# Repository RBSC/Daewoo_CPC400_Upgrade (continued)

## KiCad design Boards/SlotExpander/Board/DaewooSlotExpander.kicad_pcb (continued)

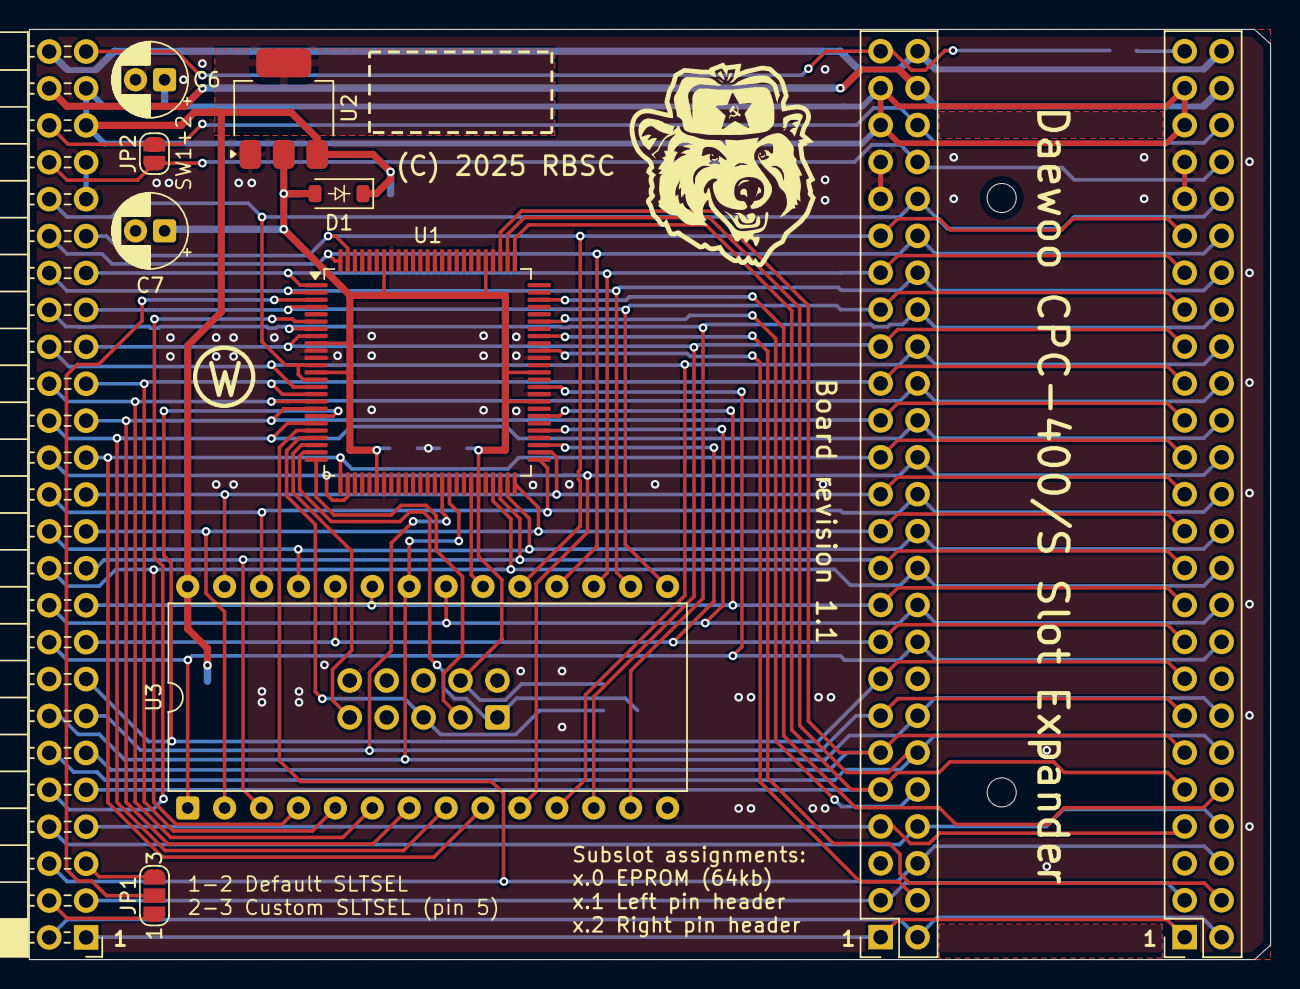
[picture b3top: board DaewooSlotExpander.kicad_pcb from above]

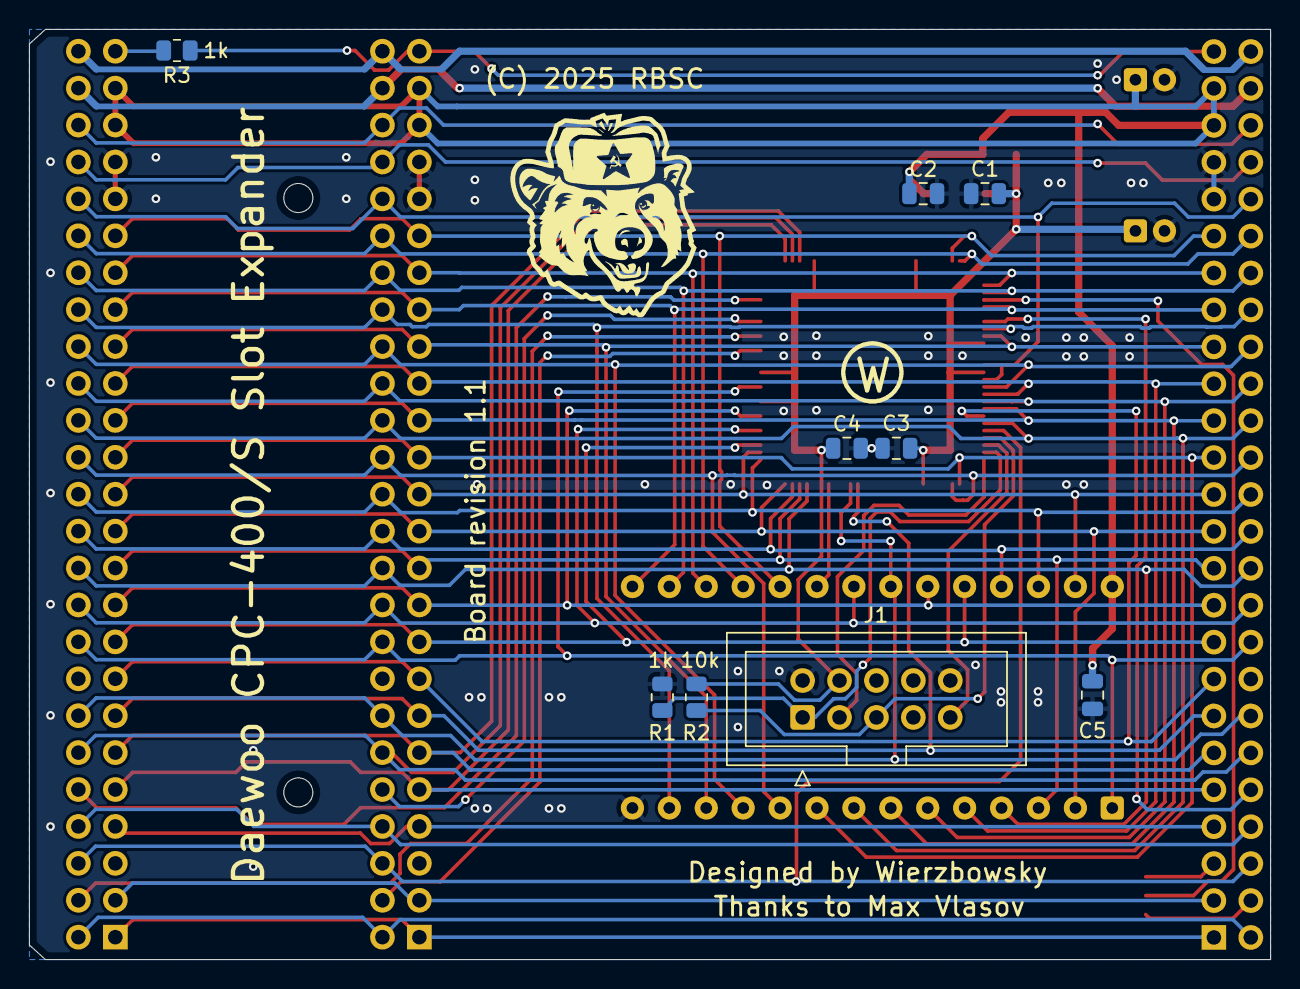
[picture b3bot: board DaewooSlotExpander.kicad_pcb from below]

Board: 2 copper layers, 85.4 x 64.0 mm, 20 parts (9 on the bottom side), 59 nets.

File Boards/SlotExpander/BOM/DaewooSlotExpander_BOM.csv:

"Id";"Designator";"Footprint";"Quantity";"Designation";"Supplier and ref";
1;"D1";"D_SOD-123";1;"1N4148W";;;
2;"C6,C7";"CP_Radial_D5.0mm_P2.00mm";2;"100uF 16V";;;
3;"U2";"SOT-223-3_TabPin2";1;"AMS1117-3.3";;;
4;"U3";"DIP-28_W15.24mm";1;"27C512";;;
5;"BUS_Expansion2,BUS_Expansion3";"PinHeader_2x25_P2.54mm_Vertical";2;"my_components_MSX_SLOT_HOST";;;
6;"BUS_Expansion1";"DaewooBackSlotConnector";1;"my_components_MSX_SLOT_HOST";;;
7;"U1";"LQFP-100_14x14mm_P0.5mm";1;"EPM240T100";;;
8;"C2,C5,C1,C3,C4";"C_0805_2012Metric";5;"100nF";;;
9;"J1";"IDC-Header_2x05_P2.54mm_Vertical";1;"AVR-JTAG-10";;;
10;"R2";"R_0805_2012Metric";1;"10k";;;
11;"R1,R3";"R_0805_2012Metric";2;"1k";;;

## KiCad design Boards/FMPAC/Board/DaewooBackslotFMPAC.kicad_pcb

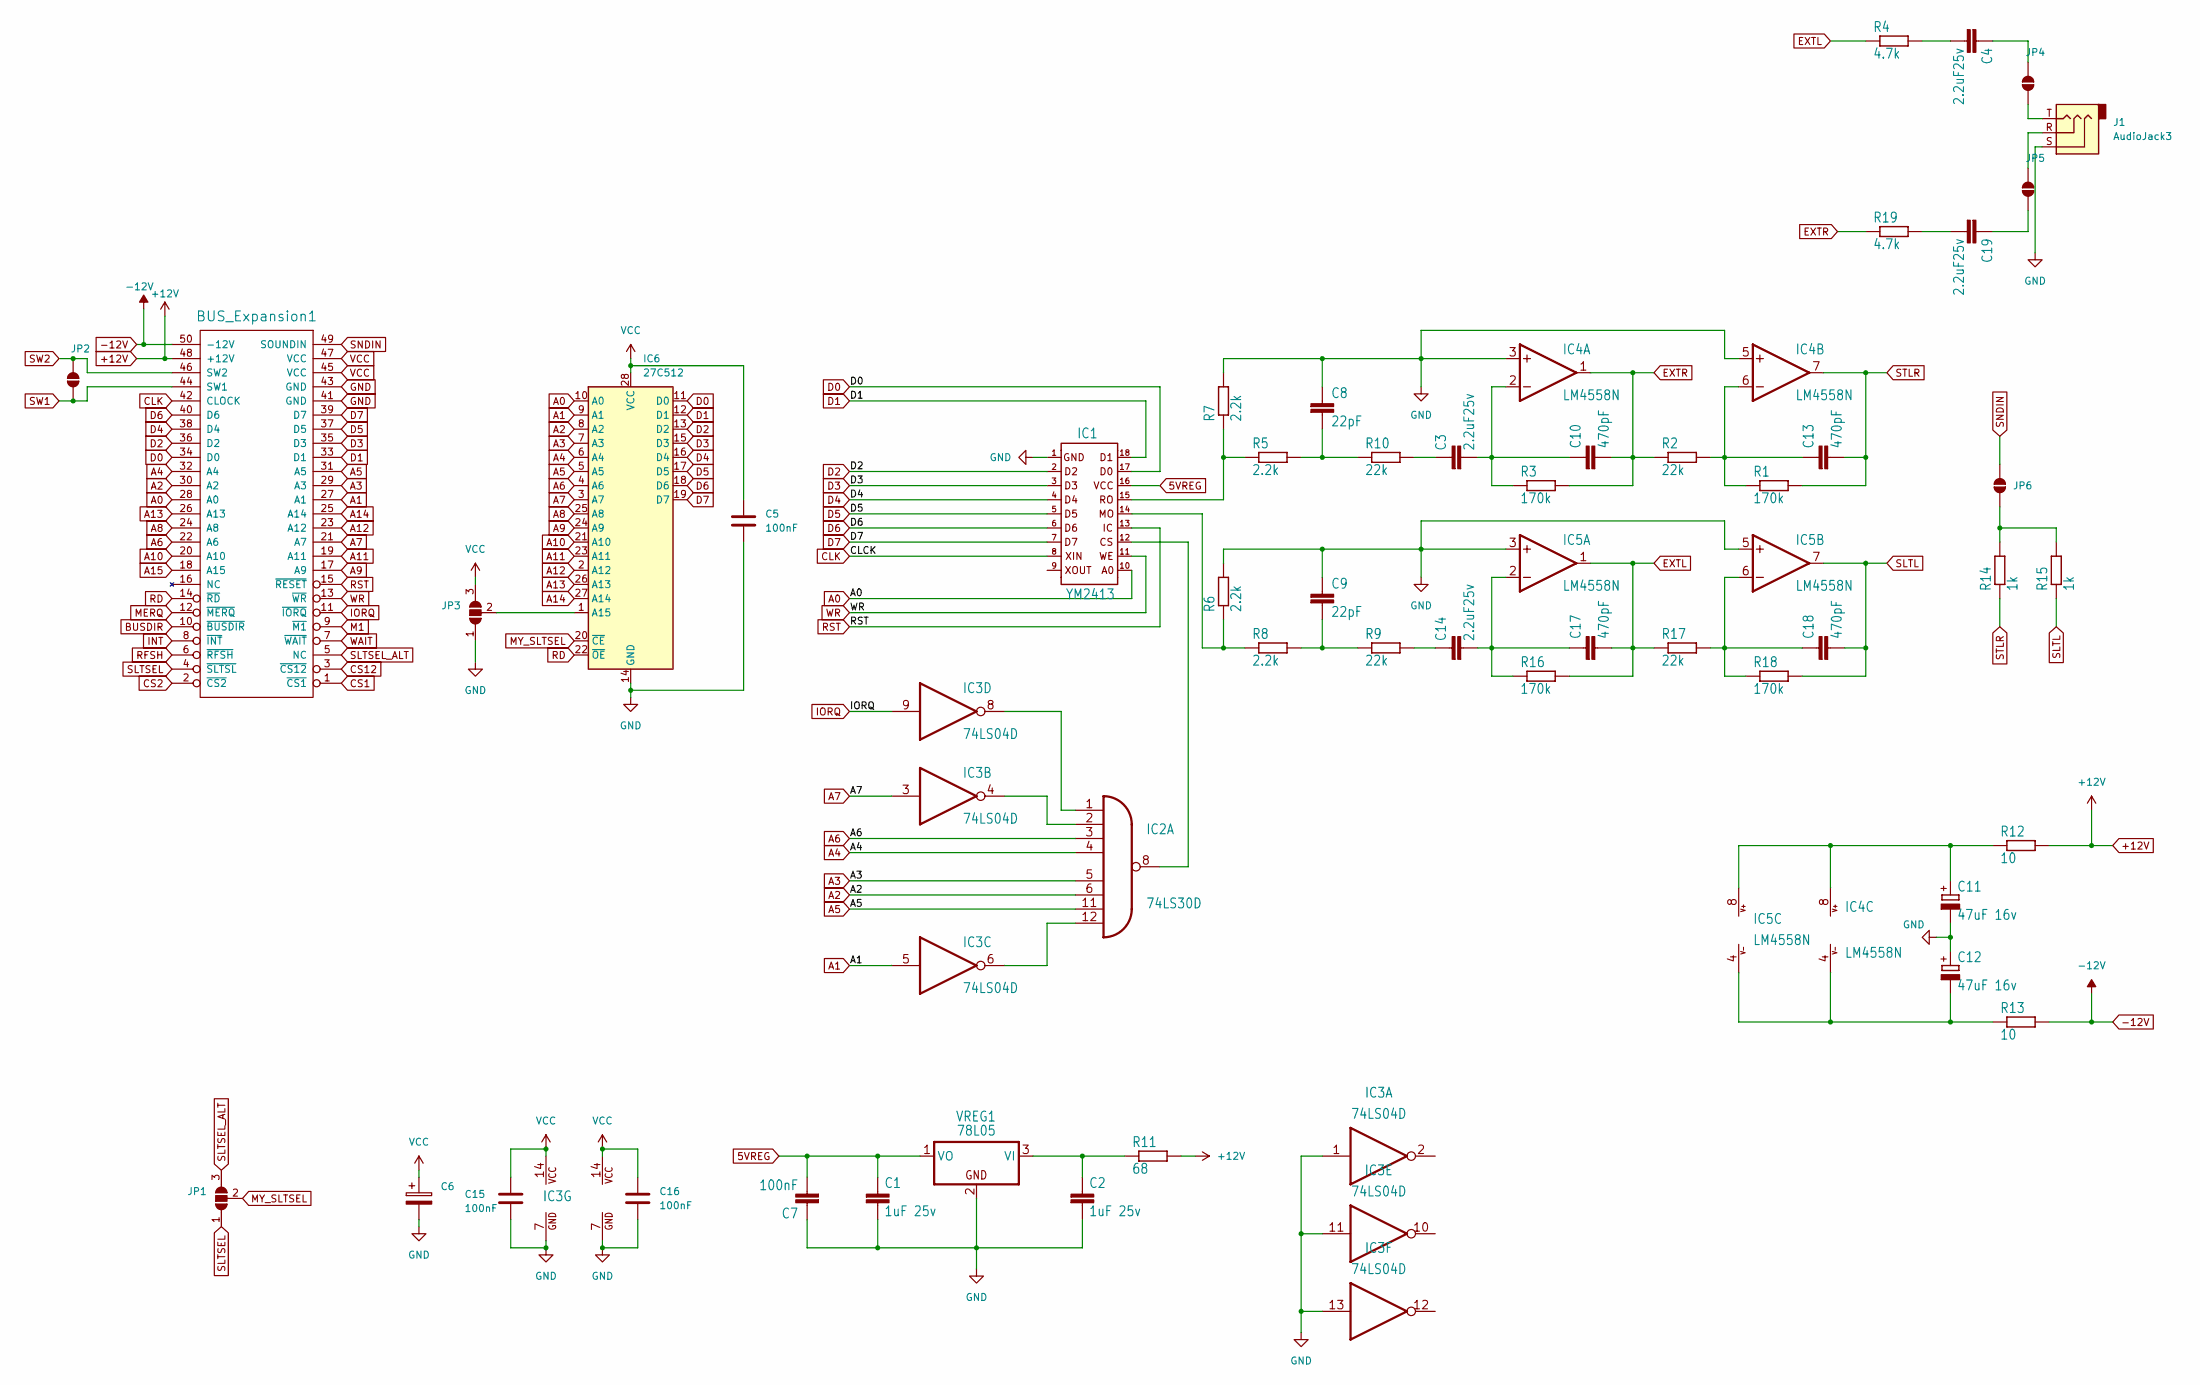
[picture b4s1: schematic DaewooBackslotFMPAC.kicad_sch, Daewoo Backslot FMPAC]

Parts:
BUS_Expansion1: my_components_MSX_SLOT_HOST; DaewooBackSlotConnector
C1, C2: 1uF 25v; C_1210_3225Metric
C3, C4, C14, C19: 2.2uF25v; C_1210_3225Metric
C5, C7, C15, C16: 100nF; C_0805_2012Metric
C6: 100uF 16V; CP_Radial_D5.0mm_P2.00mm
C8, C9: 22pF; C_0805_2012Metric
C10, C13, C17, C18: 470pF; C_0805_2012Metric
C11, C12: 47uF 16v; CP_Radial_D5.0mm_P2.00mm
IC1: YM2413; DIP-18_W7.62mm_LongPads
IC2: 74LS30D; SO-14_3.9x8.65mm_P1.27mm
IC3: 74LS04D; SO-14_3.9x8.65mm_P1.27mm
IC4, IC5: LM4558N; SOIC-8_3.9x4.9mm_P1.27mm
IC6: 27C512; DIP-28_W15.24mm
J1: AudioJack3; Jack_3.5mm_CUI_SJ1-3525N_Horizontal
JP1, JP3: SolderJumper_3_Open; SolderJumper-3_P1.3mm_Open_RoundedPad1.0x1.5mm_NumberLabels
JP2, JP4, JP5, JP6: SolderJumper_2_Open; SolderJumper-2_P1.3mm_Open_RoundedPad1.0x1.5mm
R1, R3, R16, R18: 170k; R_0805_2012Metric
R2, R9, R10, R17: 22k; R_0805_2012Metric
R4, R19: 4.7k; R_0805_2012Metric
R5, R6, R7, R8: 2.2k; R_0805_2012Metric
R11: 68; R_0805_2012Metric
R12, R13: 10; R_0805_2012Metric
R14, R15: 1k; R_0805_2012Metric
VREG1: 78L05; TO-92

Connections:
5VREG: C1.1, C7.2, IC1.16, VREG1.1 (VO)
+12V: BUS_Expansion1.48 (+12V), C11.1, R11.2, R12.2
-12V: BUS_Expansion1.50 (-12V), C12.2, R13.2
A0: BUS_Expansion1.28 (A0), IC1.10, IC6.10 (A0)
A1: BUS_Expansion1.27 (A1), IC3.5 (I), IC6.9 (A1)
A2: BUS_Expansion1.30 (A2), IC2.6 (I5), IC6.8 (A2)
A3: BUS_Expansion1.29 (A3), IC2.5 (I4), IC6.7 (A3)
A4: BUS_Expansion1.32 (A4), IC2.4 (I3), IC6.6 (A4)
A5: BUS_Expansion1.31 (A5), IC2.11 (I6), IC6.5 (A5)
A6: BUS_Expansion1.22 (A6), IC2.3 (I2), IC6.4 (A6)
A7: BUS_Expansion1.21 (A7), IC3.3 (I), IC6.3 (A7)
A8: BUS_Expansion1.24 (A8), IC6.25 (A8)
A9: BUS_Expansion1.17 (A9), IC6.24 (A9)
A10: BUS_Expansion1.20 (A10), IC6.21 (A10)
A11: BUS_Expansion1.19 (A11), IC6.23 (A11)
A12: BUS_Expansion1.23 (A12), IC6.2 (A12)
A13: BUS_Expansion1.26 (A13), IC6.26 (A13)
A14: BUS_Expansion1.25 (A14), IC6.27 (A14)
A15: BUS_Expansion1.18 (A15)
BUSDIR: BUS_Expansion1.10 (~BUSDIR)
CLK: BUS_Expansion1.42 (CLOCK), IC1.8
CS1: BUS_Expansion1.1 (~CS1)
CS2: BUS_Expansion1.2 (~CS2)
CS12: BUS_Expansion1.3 (~CS12)
D0: BUS_Expansion1.34 (D0), IC1.17, IC6.11 (D0)
D1: BUS_Expansion1.33 (D1), IC1.18, IC6.12 (D1)
D2: BUS_Expansion1.36 (D2~), IC1.2, IC6.13 (D2)
D3: BUS_Expansion1.35 (D3), IC1.3, IC6.15 (D3)
D4: BUS_Expansion1.38 (D4), IC1.4, IC6.16 (D4)
D5: BUS_Expansion1.37 (D5), IC1.5, IC6.17 (D5)
D6: BUS_Expansion1.40 (D6), IC1.6, IC6.18 (D6)
D7: BUS_Expansion1.39 (D7), IC1.7, IC6.19 (D7)
EXTL: C17.2, IC5.1 (OUT), R4.1, R16.2, R17.1
EXTR: C10.2, IC4.1 (OUT), R2.1, R3.2, R19.1
GND: BUS_Expansion1.41 (GND), BUS_Expansion1.43 (GND), C1.2, C2.2, C5.2, C6.2, C7.1, C8.1, C9.1, C11.-, C12.+, C15.2, C16.2, IC1.1, IC2.7 (GND), IC3.1 (I), IC3.7 (GND), IC3.11 (I), IC3.13 (I), IC4.3 (+IN), IC4.5 (+IN), IC5.3 (+IN), IC5.5 (+IN), IC6.14 (GND), J1.S, JP3.1 (A), R6.2, R7.2, VREG1.2 (GND)
INT: BUS_Expansion1.8 (~INT)
IORQ: BUS_Expansion1.11 (~IORQ), IC3.9 (I)
M1: BUS_Expansion1.9 (~M1)
MERQ: BUS_Expansion1.12 (~MERQ)
MY_SLTSEL: IC6.20 (~CE), JP1.2 (C)
unnamed: C3.1, R10.2
unnamed: C4.2, R4.2
unnamed: C8.2, R5.2, R10.1
unnamed: C9.2, R8.2, R9.1
unnamed: C14.1, R9.2
unnamed: C19.2, R19.2
unnamed: IC1.14, R6.1, R8.1
unnamed: IC1.15, R5.1, R7.1
unnamed: IC2.1 (I0), IC3.8 (O)
unnamed: IC2.2 (I1), IC3.4 (O)
unnamed: IC2.12 (I7), IC3.6 (O)
unnamed: IC1.12, IC2.8 (O)
unnamed: C3.2, C10.1, IC4.2 (-IN), R3.1
unnamed: C13.1, IC4.6 (-IN), R1.1, R2.2
unnamed: C11.+, IC4.8 (V+), IC5.8 (V+), R12.1
unnamed: C12.-, IC4.4 (V-), IC5.4 (V-), R13.1
unnamed: C14.2, C17.1, IC5.2 (-IN), R16.1
unnamed: C18.1, IC5.6 (-IN), R17.2, R18.1
unnamed: IC6.1 (A15), JP3.2 (C)
unnamed: J1.T, JP4.1 (A)
unnamed: C4.1, JP4.2 (B)
unnamed: C19.1, JP5.1 (A)
unnamed: J1.R, JP5.2 (B)
unnamed: JP6.1 (A), R14.2, R15.2
unnamed: C2.1, R11.1, VREG1.3 (VI)
RD: BUS_Expansion1.14 (~RD), IC6.22 (~OE)
RFSH: BUS_Expansion1.6 (~RFSH)
RST: BUS_Expansion1.15 (~RESET), IC1.13
SLTL: C18.2, IC5.7 (OUT), R15.1, R18.2
SLTSEL: BUS_Expansion1.4 (~SLTSL), JP1.1 (A)
SLTSEL_ALT: BUS_Expansion1.5 (NC), JP1.3 (B)
SNDIN: BUS_Expansion1.49 (SOUNDIN), JP6.2 (B)
STLR: C13.2, IC4.7 (OUT), R1.2, R14.1
SW1: BUS_Expansion1.44 (SW1), JP2.1 (A)
SW2: BUS_Expansion1.46 (SW2), JP2.2 (B)
VCC: BUS_Expansion1.45 (VCC), BUS_Expansion1.47 (VCC), C5.1, C6.1, C15.1, C16.1, IC2.14 (VCC), IC3.14 (VCC), IC6.28 (VCC), JP3.3 (B)
WAIT: BUS_Expansion1.7 (~WAIT)
WR: BUS_Expansion1.13 (~WR), IC1.11

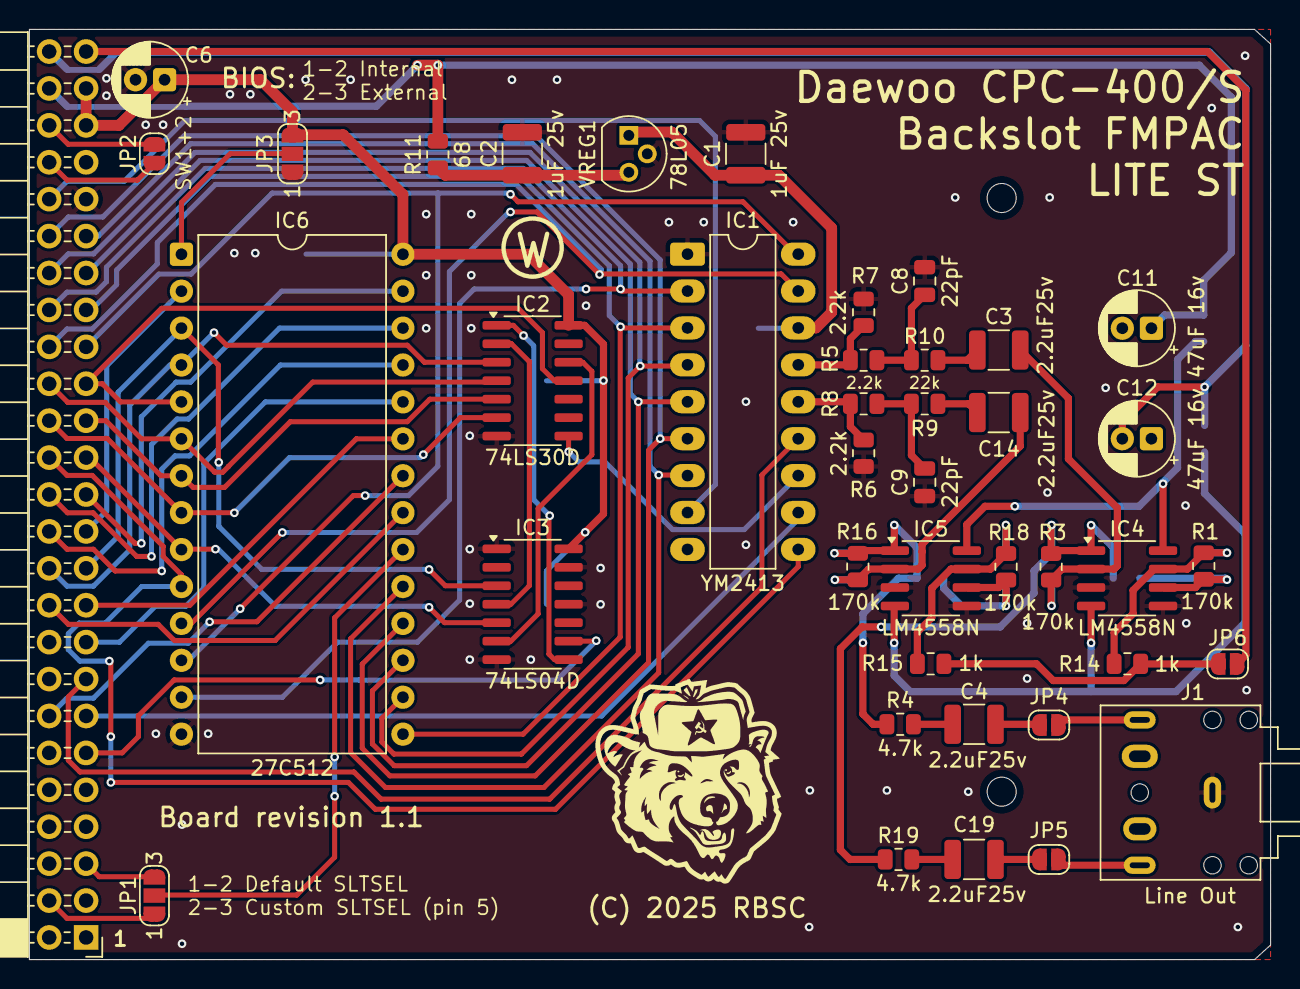
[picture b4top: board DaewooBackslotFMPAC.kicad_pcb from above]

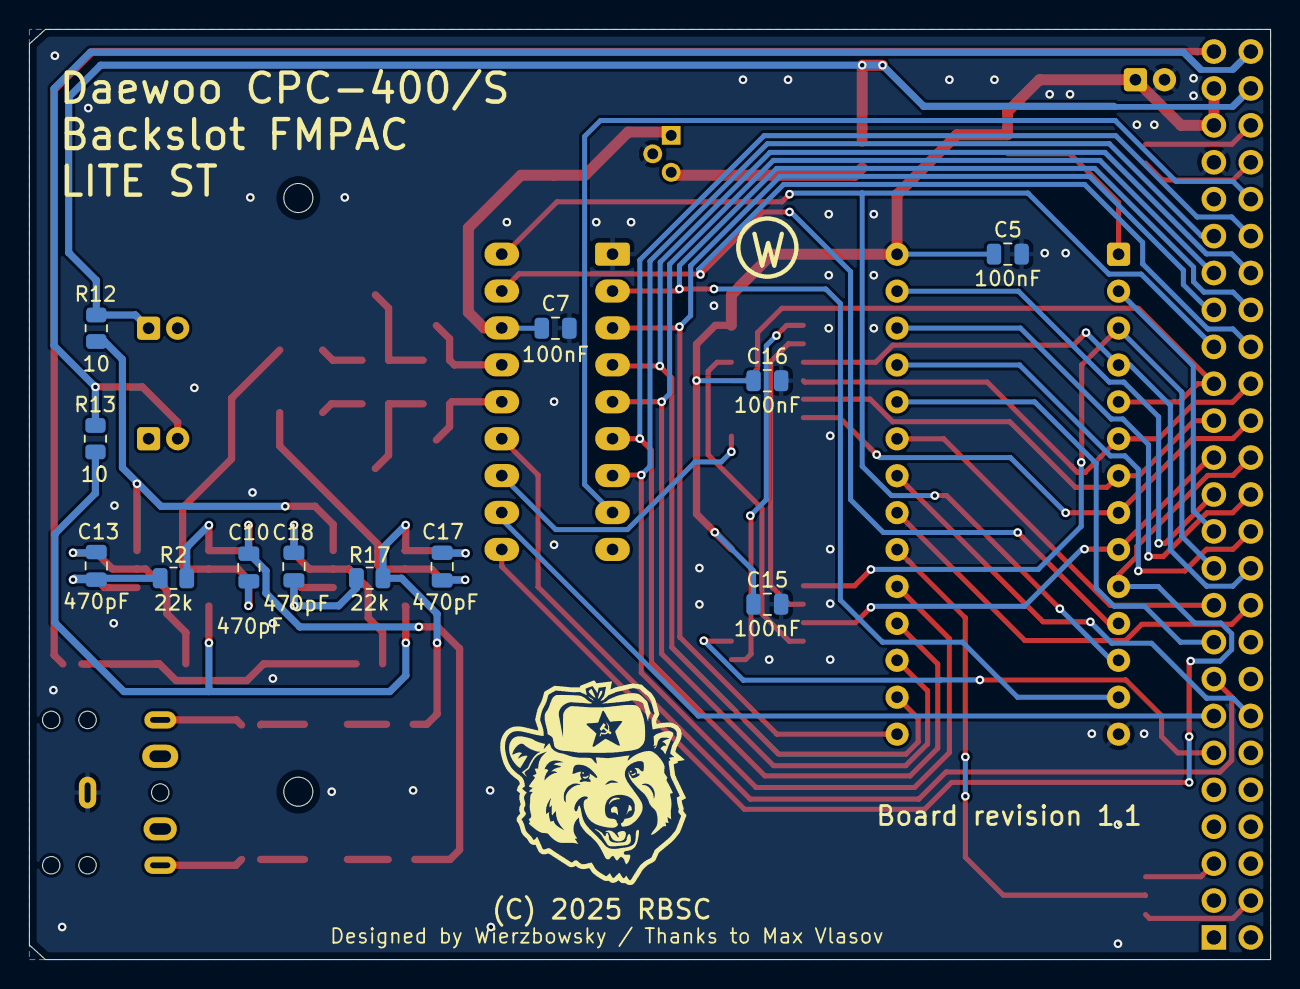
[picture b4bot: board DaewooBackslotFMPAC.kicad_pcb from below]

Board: 2 copper layers, 85.4 x 64.0 mm, 53 parts (12 on the bottom side), 68 nets.

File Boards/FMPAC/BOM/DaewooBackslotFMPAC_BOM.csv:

"Id";"Designator";"Footprint";"Quantity";"Designation";"Supplier and ref";
1;"J1";"Jack_3.5mm_CUI_SJ1-3525N_Horizontal";1;"Line Out";;;
2;"VREG1";"TO-92";1;"78L05";;;
3;"C9,C8";"C_0805_2012Metric";2;"22pF";;;
4;"R8,R5,R6,R7";"R_0805_2012Metric";4;"2.2k";;;
5;"IC1";"DIP-18_W7.62mm_LongPads";1;"YM2413";;;
6;"IC4,IC5";"SOIC-8_3.9x4.9mm_P1.27mm";2;"LM4558N";;;
7;"C12,C11";"CP_Radial_D5.0mm_P2.00mm";2;"47uF 16v";;;
8;"C1,C2";"C_1210_3225Metric";2;"1uF 25v";;;
9;"R19,R4";"R_0805_2012Metric";2;"4.7k";;;
10;"R16,R3,R1,R18";"R_0805_2012Metric";4;"170k";;;
11;"R11";"R_0805_2012Metric";1;"68";;;
12;"C3,C14,C19,C4";"C_1210_3225Metric";4;"2.2uF25v";;;
13;"IC2";"SO-14_3.9x8.65mm_P1.27mm";1;"74LS30D";;;
14;"R9,R10,R17,R2";"R_0805_2012Metric";4;"22k";;;
15;"C6";"CP_Radial_D5.0mm_P2.00mm";1;"100uF 16V";;;
16;"IC6";"DIP-28_W15.24mm";1;"27C512";;;
17;"IC3";"SO-14_3.9x8.65mm_P1.27mm";1;"74LS04D";;;
18;"BUS_Expansion1";"DaewooBackSlotConnector";1;"my_components_MSX_SLOT_HOST";;;
19;"C10,C13,C17,C18";"C_0805_2012Metric";4;"470pF";;;
20;"R12,R13";"R_0805_2012Metric";2;"10";;;
21;"C15,C5,C7,C16";"C_0805_2012Metric";4;"100nF";;;
22;"R14,R15";"R_0805_2012Metric";2;"1k";;;

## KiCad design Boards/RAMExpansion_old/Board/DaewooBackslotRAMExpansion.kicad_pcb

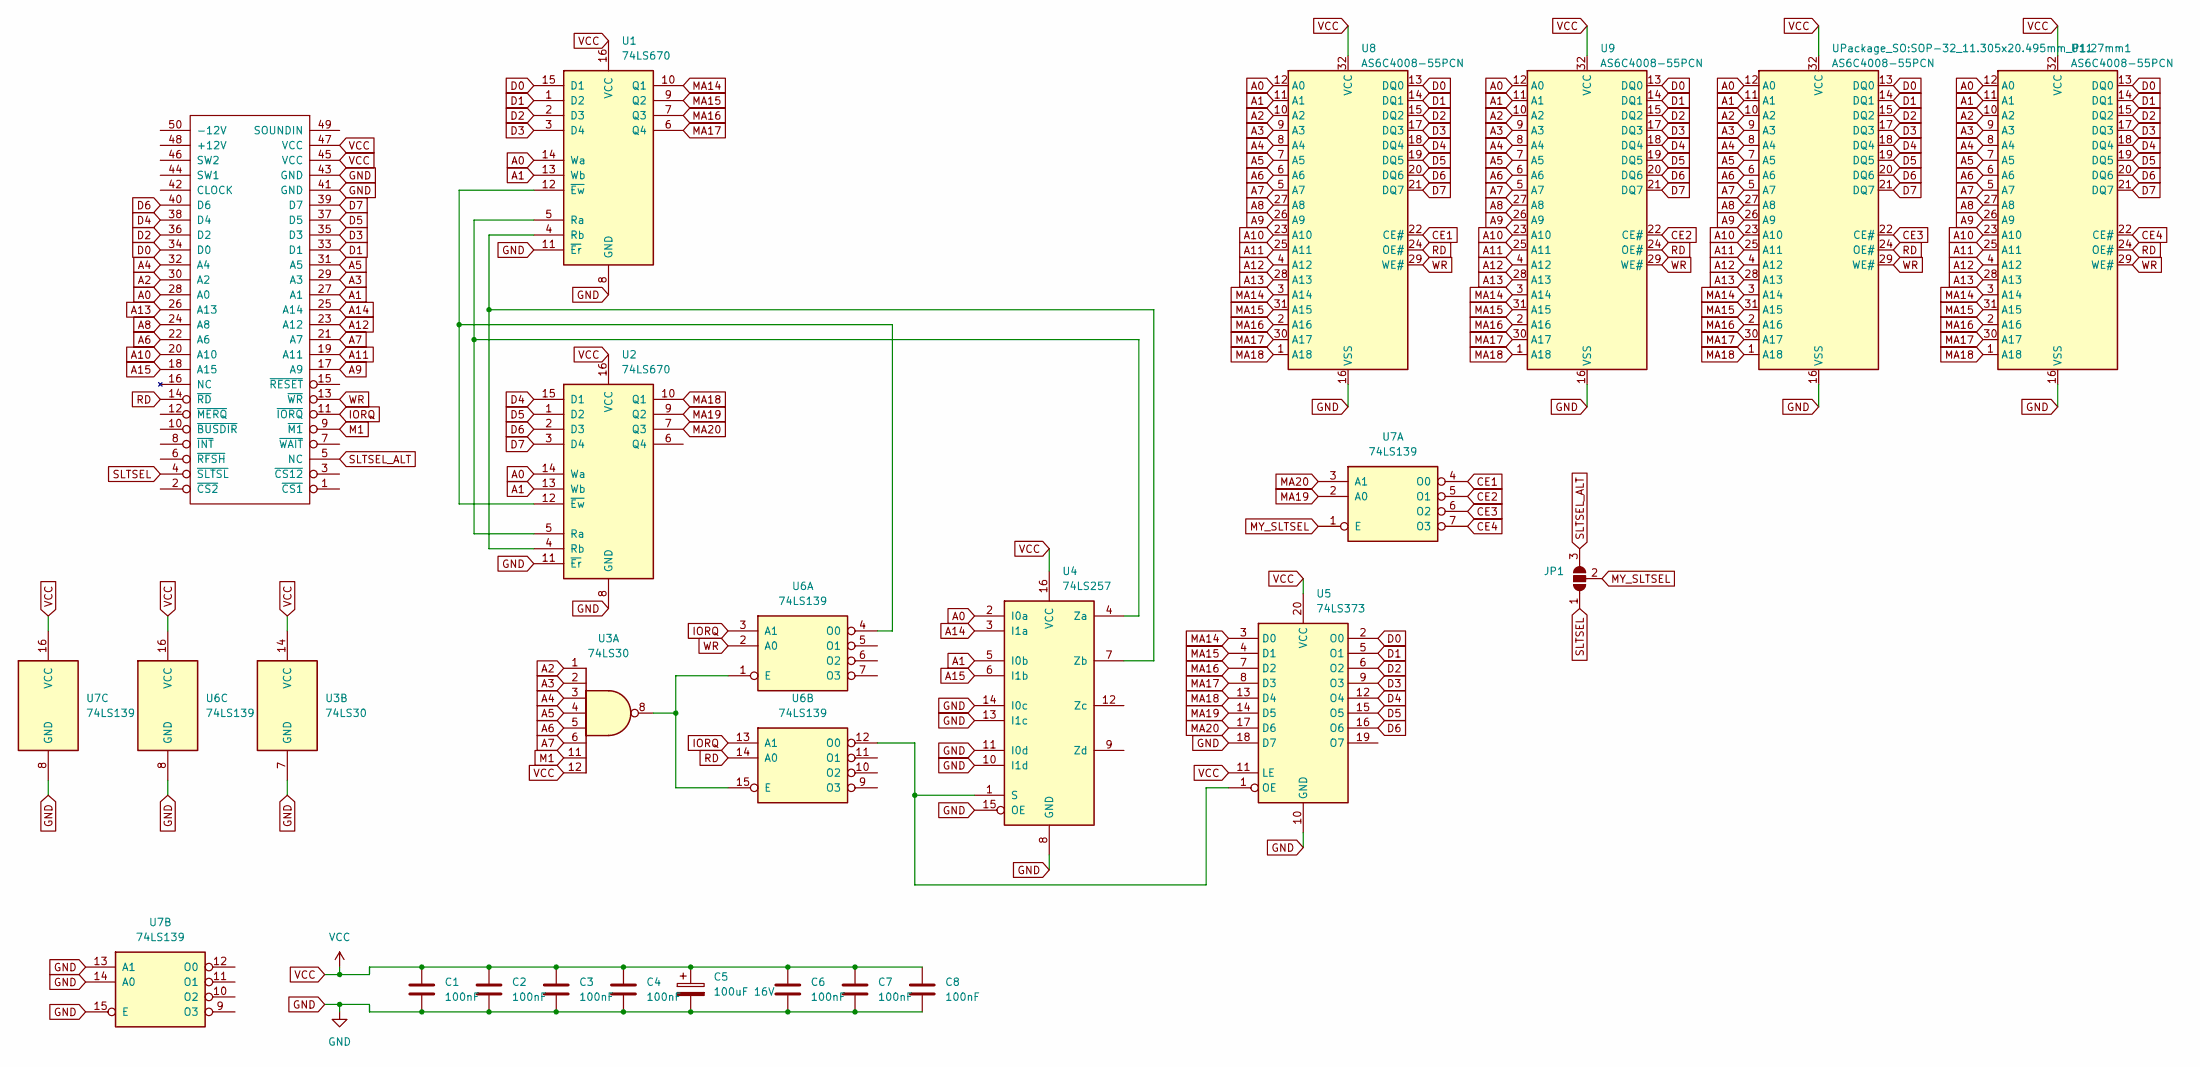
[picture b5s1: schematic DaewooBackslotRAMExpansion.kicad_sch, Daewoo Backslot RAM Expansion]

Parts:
BUS1: my_components_MSX_SLOT_HOST; DaewooBackSlotConnector
C1, C2, C3, C4, C6, C7, C8: 100nF; C_0805_2012Metric
C5: 100uF 16V; CP_Radial_D5.0mm_P2.00mm
JP1: SolderJumper_3_Open; SolderJumper-3_P1.3mm_Open_RoundedPad1.0x1.5mm_NumberLabels
U1, U2: 74LS670; SO-16_3.9x9.9mm_P1.27mm
U3: 74LS30; SO-14_3.9x8.65mm_P1.27mm
U4: 74LS257; SO-16_3.9x9.9mm_P1.27mm
U5: 74LS373; SOIC-20W_7.5x12.8mm_P1.27mm
U6, U7: 74LS139; SO-16_3.9x9.9mm_P1.27mm
U8, U9, U11: AS6C4008-55PCN; SOP-32_11.305x20.495mm_P1.27mm
UPackage_SO:SOP-32_11.305x20.495mm_P1.27mm1: AS6C4008-55PCN; SOP-32_11.305x20.495mm_P1.27mm

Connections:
A0: BUS1.28 (A0), U1.14 (Wa), U2.14 (Wa), U4.2 (I0a), U8.12 (A0), U9.12 (A0), U11.12 (A0), UPackage_SO:SOP-32_11.305x20.495mm_P1.2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.12 (A0); also elsewhere on the board
A1: BUS1.27 (A1), U1.13 (Wb), U2.13 (Wb), U4.5 (I0b), U8.11 (A1), U9.11 (A1), U11.11 (A1), UPackage_SO:SOP-32_11.305x20.495mm_P1.2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.11 (A1); also elsewhere on the board
A2: BUS1.30 (A2), U3.1, U8.10 (A2), U9.10 (A2), U11.10 (A2), UPackage_SO:SOP-32_11.305x20.495mm_P1.2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.10 (A2); also elsewhere on the board
A3: BUS1.29 (A3), U3.2, U8.9 (A3), U9.9 (A3), U11.9 (A3), UPackage_SO:SOP-32_11.305x20.495mm_P1.2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.9 (A3); also elsewhere on the board
A4: BUS1.32 (A4), U3.3, U8.8 (A4), U9.8 (A4), U11.8 (A4), UPackage_SO:SOP-32_11.305x20.495mm_P1.2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.8 (A4); also elsewhere on the board
A5: BUS1.31 (A5), U3.4, U8.7 (A5), U9.7 (A5), U11.7 (A5), UPackage_SO:SOP-32_11.305x20.495mm_P1.2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.7 (A5); also elsewhere on the board
A6: BUS1.22 (A6), U3.5, U8.6 (A6), U9.6 (A6), U11.6 (A6), UPackage_SO:SOP-32_11.305x20.495mm_P1.2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.6 (A6); also elsewhere on the board
A7: BUS1.21 (A7), U3.6, U8.5 (A7), U9.5 (A7), U11.5 (A7), UPackage_SO:SOP-32_11.305x20.495mm_P1.2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.5 (A7); also elsewhere on the board
A8: BUS1.24 (A8), U8.27 (A8), U9.27 (A8), U11.27 (A8), UPackage_SO:SOP-32_11.305x20.495mm_P1.2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.27 (A8); also elsewhere on the board
A9: BUS1.17 (A9), U8.26 (A9), U9.26 (A9), U11.26 (A9), UPackage_SO:SOP-32_11.305x20.495mm_P1.2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.26 (A9); also elsewhere on the board
A10: BUS1.20 (A10), U8.23 (A10), U9.23 (A10), U11.23 (A10), UPackage_SO:SOP-32_11.305x20.495mm_P1.2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.23 (A10); also elsewhere on the board
A11: BUS1.19 (A11), U8.25 (A11), U9.25 (A11), U11.25 (A11), UPackage_SO:SOP-32_11.305x20.495mm_P1.2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.25 (A11); also elsewhere on the board
A12: BUS1.23 (A12), U8.4 (A12), U9.4 (A12), U11.4 (A12), UPackage_SO:SOP-32_11.305x20.495mm_P1.2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.4 (A12); also elsewhere on the board
A13: BUS1.26 (A13), U8.28 (A13), U9.28 (A13), U11.28 (A13), UPackage_SO:SOP-32_11.305x20.495mm_P1.2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.28 (A13); also elsewhere on the board
A14: BUS1.25 (A14), U4.3 (I1a)
A15: BUS1.18 (A15), U4.6 (I1b)
CE1: U7.4 (O0), U8.22 (CE#)
CE2: U7.5 (O1), U9.22 (CE#)
CE3: U7.6 (O2), UPackage_SO:SOP-32_11.305x20.495mm_P1.2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.22 (CE#); also elsewhere on the board
CE4: U7.7 (O3), U11.22 (CE#)
D0: BUS1.34 (D0), U1.15 (D1), U5.2 (O0), U8.13 (DQ0), U9.13 (DQ0), U11.13 (DQ0), UPackage_SO:SOP-32_11.305x20.495mm_P1.2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.13 (DQ0); also elsewhere on the board
D1: BUS1.33 (D1), U1.1 (D2), U5.5 (O1), U8.14 (DQ1), U9.14 (DQ1), U11.14 (DQ1), UPackage_SO:SOP-32_11.305x20.495mm_P1.2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.14 (DQ1); also elsewhere on the board
D2: BUS1.36 (D2~), U1.2 (D3), U5.6 (O2), U8.15 (DQ2), U9.15 (DQ2), U11.15 (DQ2), UPackage_SO:SOP-32_11.305x20.495mm_P1.2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.15 (DQ2); also elsewhere on the board
D3: BUS1.35 (D3), U1.3 (D4), U5.9 (O3), U8.17 (DQ3), U9.17 (DQ3), U11.17 (DQ3), UPackage_SO:SOP-32_11.305x20.495mm_P1.2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.17 (DQ3); also elsewhere on the board
D4: BUS1.38 (D4), U2.15 (D1), U5.12 (O4), U8.18 (DQ4), U9.18 (DQ4), U11.18 (DQ4), UPackage_SO:SOP-32_11.305x20.495mm_P1.2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.18 (DQ4); also elsewhere on the board
D5: BUS1.37 (D5), U2.1 (D2), U5.15 (O5), U8.19 (DQ5), U9.19 (DQ5), U11.19 (DQ5), UPackage_SO:SOP-32_11.305x20.495mm_P1.2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.19 (DQ5); also elsewhere on the board
D6: BUS1.40 (D6), U2.2 (D3), U5.16 (O6), U8.20 (DQ6), U9.20 (DQ6), U11.20 (DQ6), UPackage_SO:SOP-32_11.305x20.495mm_P1.2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.20 (DQ6); also elsewhere on the board
D7: BUS1.39 (D7), U2.3 (D4), U8.21 (DQ7), U9.21 (DQ7), U11.21 (DQ7), UPackage_SO:SOP-32_11.305x20.495mm_P1.2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.21 (DQ7); also elsewhere on the board
GND: BUS1.41 (GND), BUS1.43 (GND), C1.2, C2.2, C3.2, C4.2, C5.2, C6.2, C7.2, C8.2, U1.8 (GND), U1.11 (~Er), U2.8 (GND), U2.11 (~Er), U3.7 (GND), U4.8 (GND), U4.10 (I1d), U4.11 (I0d), U4.13 (I1c), U4.14 (I0c), U4.15 (OE), U5.10 (GND), U5.18 (D7), U6.8 (GND), U7.8 (GND), U7.13 (A1), U7.14 (A0), U7.15 (E), U8.16 (VSS), U9.16 (VSS), U11.16 (VSS), UPackage_SO:SOP-32_11.305x20.495mm_P1.2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.16 (VSS); also elsewhere on the board
IORQ: BUS1.11 (~IORQ), U6.3 (A1), U6.13 (A1)
M1: BUS1.9 (~M1), U3.11
MA14: U1.10 (Q1), U5.3 (D0), U8.3 (A14), U9.3 (A14), U11.3 (A14), UPackage_SO:SOP-32_11.305x20.495mm_P1.2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.3 (A14); also elsewhere on the board
MA15: U1.9 (Q2), U5.4 (D1), U8.31 (A15), U9.31 (A15), U11.31 (A15), UPackage_SO:SOP-32_11.305x20.495mm_P1.2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.31 (A15); also elsewhere on the board
MA16: U1.7 (Q3), U5.7 (D2), U8.2 (A16), U9.2 (A16), U11.2 (A16), UPackage_SO:SOP-32_11.305x20.495mm_P1.2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.2 (A16); also elsewhere on the board
MA17: U1.6 (Q4), U5.8 (D3), U8.30 (A17), U9.30 (A17), U11.30 (A17), UPackage_SO:SOP-32_11.305x20.495mm_P1.2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.30 (A17); also elsewhere on the board
MA18: U2.10 (Q1), U5.13 (D4), U8.1 (A18), U9.1 (A18), U11.1 (A18), UPackage_SO:SOP-32_11.305x20.495mm_P1.2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.1 (A18); also elsewhere on the board
MA19: U2.9 (Q2), U5.14 (D5), U7.2 (A0)
MA20: U2.7 (Q3), U5.17 (D6), U7.3 (A1)
MY_SLTSEL: JP1.2 (C), U7.1 (E)
unnamed: U1.5 (Ra), U2.5 (Ra), U4.4 (Za)
unnamed: U1.4 (Rb), U2.4 (Rb), U4.7 (Zb)
unnamed: U1.12 (~Ew), U2.12 (~Ew), U6.4 (O0)
unnamed: U4.1 (S), U5.1 (OE), U6.12 (O0)
unnamed: U3.8, U6.1 (E), U6.15 (E)
RD: BUS1.14 (~RD), U6.14 (A0), U8.24 (OE#), U9.24 (OE#), U11.24 (OE#), UPackage_SO:SOP-32_11.305x20.495mm_P1.2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.24 (OE#); also elsewhere on the board
SLTSEL: BUS1.4 (~SLTSL), JP1.1 (A)
SLTSEL_ALT: BUS1.5 (NC), JP1.3 (B)
VCC: BUS1.45 (VCC), BUS1.47 (VCC), C1.1, C2.1, C3.1, C4.1, C5.1, C6.1, C7.1, C8.1, U1.16 (VCC), U2.16 (VCC), U3.12, U3.14 (VCC), U4.16 (VCC), U5.11 (LE), U5.20 (VCC), U6.16 (VCC), U7.16 (VCC), U8.32 (VCC), U9.32 (VCC), U11.32 (VCC), UPackage_SO:SOP-32_11.305x20.495mm_P1.2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.32 (VCC); also elsewhere on the board
WR: BUS1.13 (~WR), U6.2 (A0), U8.29 (WE#), U9.29 (WE#), U11.29 (WE#), UPackage_SO:SOP-32_11.305x20.495mm_P1.2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.29 (WE#); also elsewhere on the board

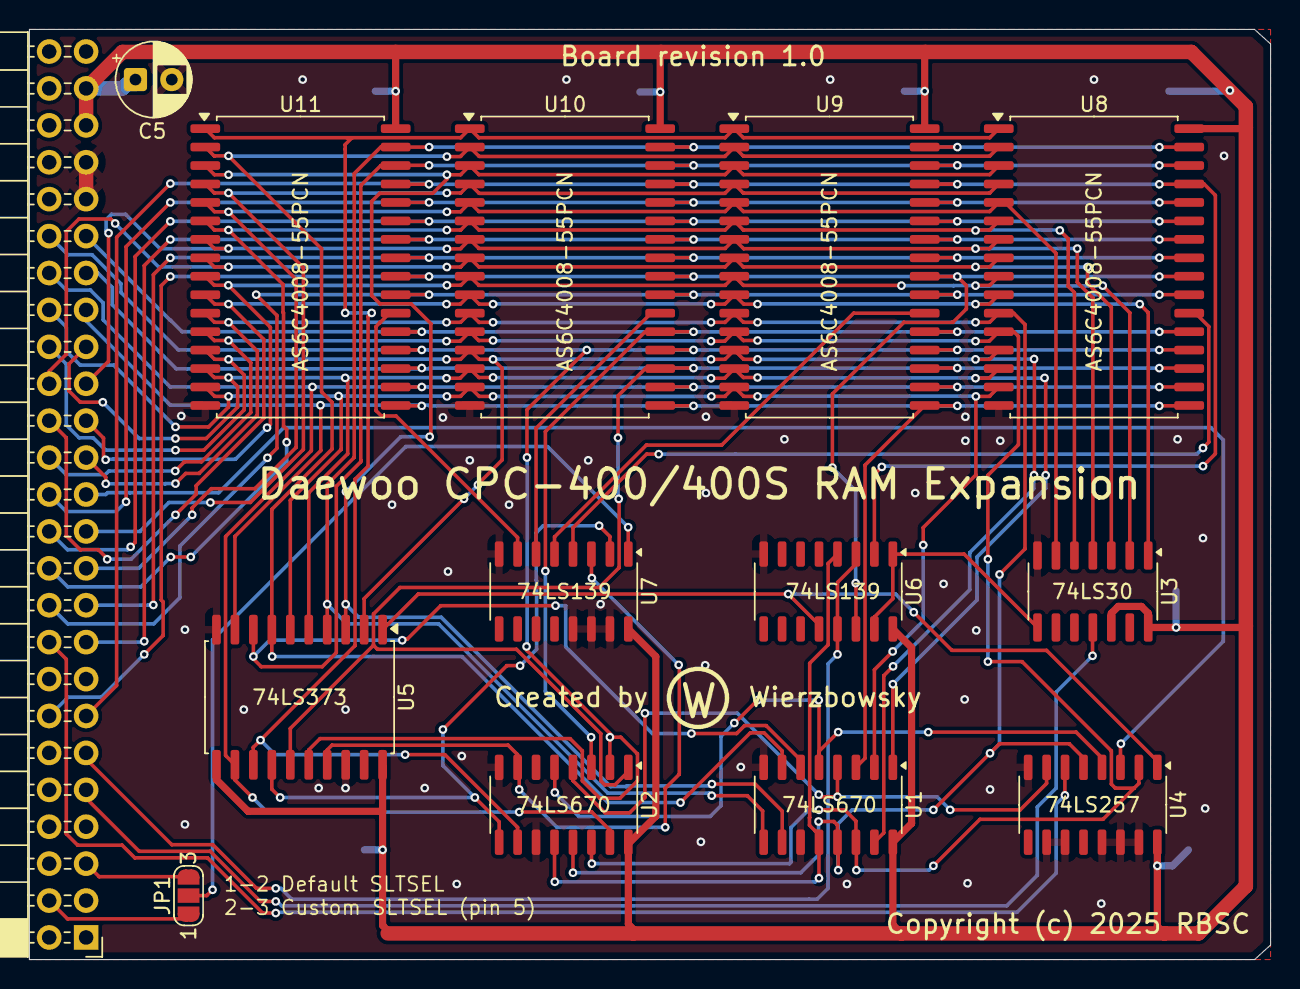
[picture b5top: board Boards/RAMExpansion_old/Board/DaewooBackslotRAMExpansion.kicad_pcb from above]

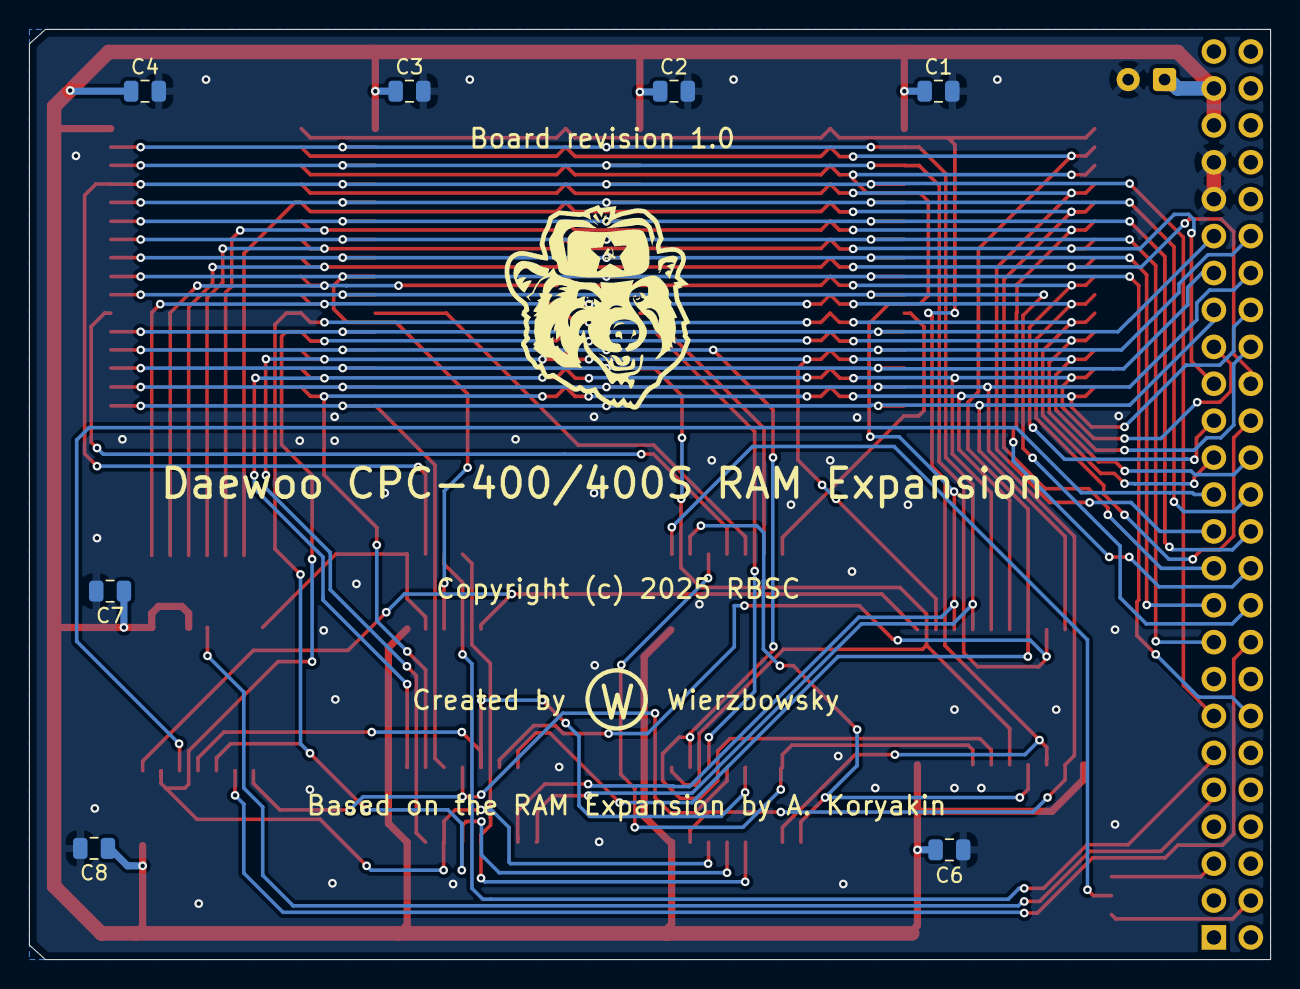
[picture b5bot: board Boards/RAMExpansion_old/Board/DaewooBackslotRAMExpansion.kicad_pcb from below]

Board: 2 copper layers, 85.4 x 64.0 mm, 21 parts (7 on the bottom side), 49 nets.

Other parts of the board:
U10: AS6C4008-55PCN; SOP-32_11.305x20.495mm_P1.27mm

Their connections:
A0: U10.12 (A0); also elsewhere on the board
A1: U10.11 (A1); also elsewhere on the board
A2: U10.10 (A2); also elsewhere on the board
A3: U10.9 (A3); also elsewhere on the board
A4: U10.8 (A4); also elsewhere on the board
A5: U10.7 (A5); also elsewhere on the board
A6: U10.6 (A6); also elsewhere on the board
A7: U10.5 (A7); also elsewhere on the board
A8: U10.27 (A8); also elsewhere on the board
A9: U10.26 (A9); also elsewhere on the board
A10: U10.23 (A10); also elsewhere on the board
A11: U10.25 (A11); also elsewhere on the board
A12: U10.4 (A12); also elsewhere on the board
A13: U10.28 (A13); also elsewhere on the board
CE3: U10.22 (CE#); also elsewhere on the board
D0: U10.13 (DQ0); also elsewhere on the board
D1: U10.14 (DQ1); also elsewhere on the board
D2: U10.15 (DQ2); also elsewhere on the board
D3: U10.17 (DQ3); also elsewhere on the board
D4: U10.18 (DQ4); also elsewhere on the board
D5: U10.19 (DQ5); also elsewhere on the board
D6: U10.20 (DQ6); also elsewhere on the board
D7: U10.21 (DQ7); also elsewhere on the board
GND: U10.16 (VSS); also elsewhere on the board
MA14: U10.3 (A14); also elsewhere on the board
MA15: U10.31 (A15); also elsewhere on the board
MA16: U10.2 (A16); also elsewhere on the board
MA17: U10.30 (A17); also elsewhere on the board
MA18: U10.1 (A18); also elsewhere on the board
RD: U10.24 (OE#); also elsewhere on the board
VCC: U10.32 (VCC); also elsewhere on the board
WR: U10.29 (WE#); also elsewhere on the board

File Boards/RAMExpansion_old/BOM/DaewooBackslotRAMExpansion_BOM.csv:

"Id";"Designator";"Footprint";"Quantity";"Designation";"Supplier and ref";
1;"C5";"CP_Radial_D5.0mm_P2.50mm";1;"100uF 16V";;;
2;"C6,C7,C8,C1,C2,C3,C4";"C_0805_2012Metric";7;"100nF";;;
3;"U3";"SO-14_3.9x8.65mm_P1.27mm";1;"74LS30";;;
4;"U8,U9,U11,U10";"SOP-32_11.305x20.495mm_P1.27mm";4;"AS6C4008-55PCN";;;
5;"U5";"SOIC-20W_7.5x12.8mm_P1.27mm";1;"74LS373";;;
6;"U7,U6";"SO-16_3.9x9.9mm_P1.27mm";2;"74LS139";;;
7;"U4";"SO-16_3.9x9.9mm_P1.27mm";1;"74LS257";;;
8;"U1,U2";"SO-16_3.9x9.9mm_P1.27mm";2;"74LS670";;;
9;"BUS1";"DaewooBackSlotConnector";1;"my_components_MSX_SLOT_HOST";;;

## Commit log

2026-04-05 Initial release 05.04.2026
    Initial release of the Daewoo CPC-400/400S conversion project files
2026-04-06 Initial release 06.04.2026
    Initial release of the Daewoo CPC-400/400S conversion project files
2026-04-07 Updated 07.04.2026
    Minor documentation changes
2026-04-09 Updated 09.04.2026
    Updated documentation - fixed a few typos and improved the structure for all files
2026-04-17 Updated 17.04.2026
    Added English versions of the documentation
2026-04-24 Updated 24.04.2026
    Added missing 3D models of cases. Also added slicer project files for dual-filament printing on Anycubic Kobra X printer.
